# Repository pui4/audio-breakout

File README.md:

# Audio Codec Module (WIP)
I needed an audio codec module for an upcoming secret project and there was no other designs that fit my criteria so I made my own. It was made for hackclub (specifically stardance), if you want more info on this project; check the stardance journal for it [here.](https://stardance.hackclub.com/projects/20340)

### Front

### Back

## Features
- Mono audio input
- Mono audio output
- I2C comunication
- thats pretty much it :p

## What it is
It is a breakout board for the Everest Semiconductors ES8311 Audio codec IC. It is similar to the ES8388 but this one is mono instead of stereo. The design of the PCB is largely based upon the design done by WaveShare when they intergrated this chip into one of their [ESP32 dev boards](https://github.com/waveshareteam/ESP32-S3-Touch-LCD-1.83/blob/main/schematic/ESP32-S3-Touch-LCD-1.83-schematic.pdf)

### Schematic

### PCB design

## BOM
You can find the BOM in the BOM.csv file. I have no idea if it is what is needed as it is what JLC needs for their assembly and what the JLC Kicad extension spits out. Lemme know if anything is wrong or needs changing.

## Note for reviewer
I have already uploaded it to JLC and got a price of ￡44.04 for assembly and shipping. That's around $60 for the PCB. So I am looking for a grant of $60.

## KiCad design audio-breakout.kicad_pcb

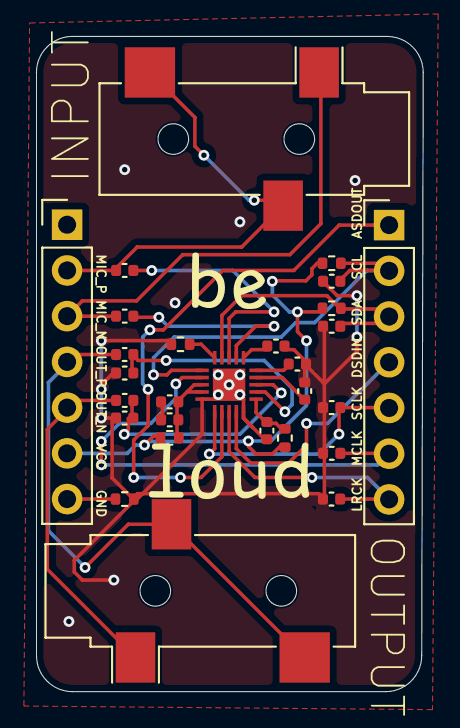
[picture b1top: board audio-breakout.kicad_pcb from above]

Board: 2 copper layers, 21.5 x 36.4 mm, 28 parts (0 on the bottom side), 24 nets.

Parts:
C1, C9, C10, C12, C13, C14, C15: 22pF; C_0402_1005Metric
C2, C3, C4, C5, C6, C7, C8, C11: 1uF; C_0402_1005Metric
C16, C17: 100nF; C_0402_1005Metric
IC1: ES8311; QFN40P300X300X60-21N
J1, J2: AudioJack3; Jack_3.5mm_CUI_SJ-3523-SMT_Horizontal
J3, J4: Conn_01x06_Pin; PinHeader_1x07_P2.54mm_Vertical
R1: 10K; R_0402_1005Metric
R2, R4: 2.2K; R_0402_1005Metric
R3, R5, R6: 0R; R_0402_1005Metric

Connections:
+3V3: J4.6, R2.1, R3.2, R4.1, R5.1
/ASDOUT: IC1.7 (ASDOUT), J3.1
/I2C_DSDIN: IC1.9 (DSDIN), J3.4
/I2C_LRCK: C14.1, IC1.8 (LRCK), J3.7
/I2C_MCLK: C12.1, IC1.2 (MCLK), J3.6
/I2C_SCLK: C13.1, IC1.6 (SCLK/DMIC_SCL), J3.5
/MIC_N: C3.2, J1.S, J4.3
/MIC_P: C2.2, J1.R, J1.T, J4.2
/OUT_N: C7.2, J2.S, J4.5
/OUT_P: C8.2, J2.R, J2.T, J4.4
/SCL: C15.1, IC1.1 (CCLK), J3.2, R4.2
/SDA: C1.1, IC1.19 (CDATA), J3.3, R2.2
GND: J4.7, R6.2
GNDA: C1.2, C4.2, C5.1, C6.1, C9.2, C10.2, C11.1, C12.2, C13.2, C14.2, C15.2, C16.2, C17.2, IC1.5 (DGND), IC1.10 (AGND), IC1.21 (EP), R1.1, R6.1
unnamed: C5.2, IC1.15 (ADCVREF)
unnamed: C11.2, IC1.11 (AVDD), R3.1
unnamed: IC1.20 (CE), R1.2
unnamed: C6.2, IC1.14 (DACVREF)
unnamed: C16.1, C17.1, IC1.3 (PVDD), IC1.4 (DVDD), R5.2
unnamed: C3.1, IC1.17 (MIC1N)
unnamed: C2.1, IC1.18 (MIC1P/DMIC_SDA)
unnamed: C7.1, C10.1, IC1.13 (OUTN)
unnamed: C8.1, C9.1, IC1.12 (OUTP)
unnamed: C4.1, IC1.16 (VMID)

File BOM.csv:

CommentDesignatorFootprintLCSCQuantity
0RR3,R5,R6R_0402_1005MetricC604853
100nFC16,C17C_0402_1005MetricC530844592
10KR1R_0402_1005MetricC604901
1uFC11,C2,C3,C4,C5,C6,C7,C8C_0402_1005MetricC15182088
2.2KR2,R4R_0402_1005MetricC29068652
22pFC1,C10,C12,C13,C14,C15,C9C_0402_1005MetricC1062037
AudioJack3J1,J2Jack_3.5mm_CUI_SJ-3523-SMT_HorizontalC49918722
ES8311IC1QFN40P300X300X60-21NC9623421
Conn_01x06_PinJ4PinHeader_1x06_P2.54mm_Vertical1
Conn_01x06_PinJ3PinHeader_1x06_P2.54mm_Vertical1
